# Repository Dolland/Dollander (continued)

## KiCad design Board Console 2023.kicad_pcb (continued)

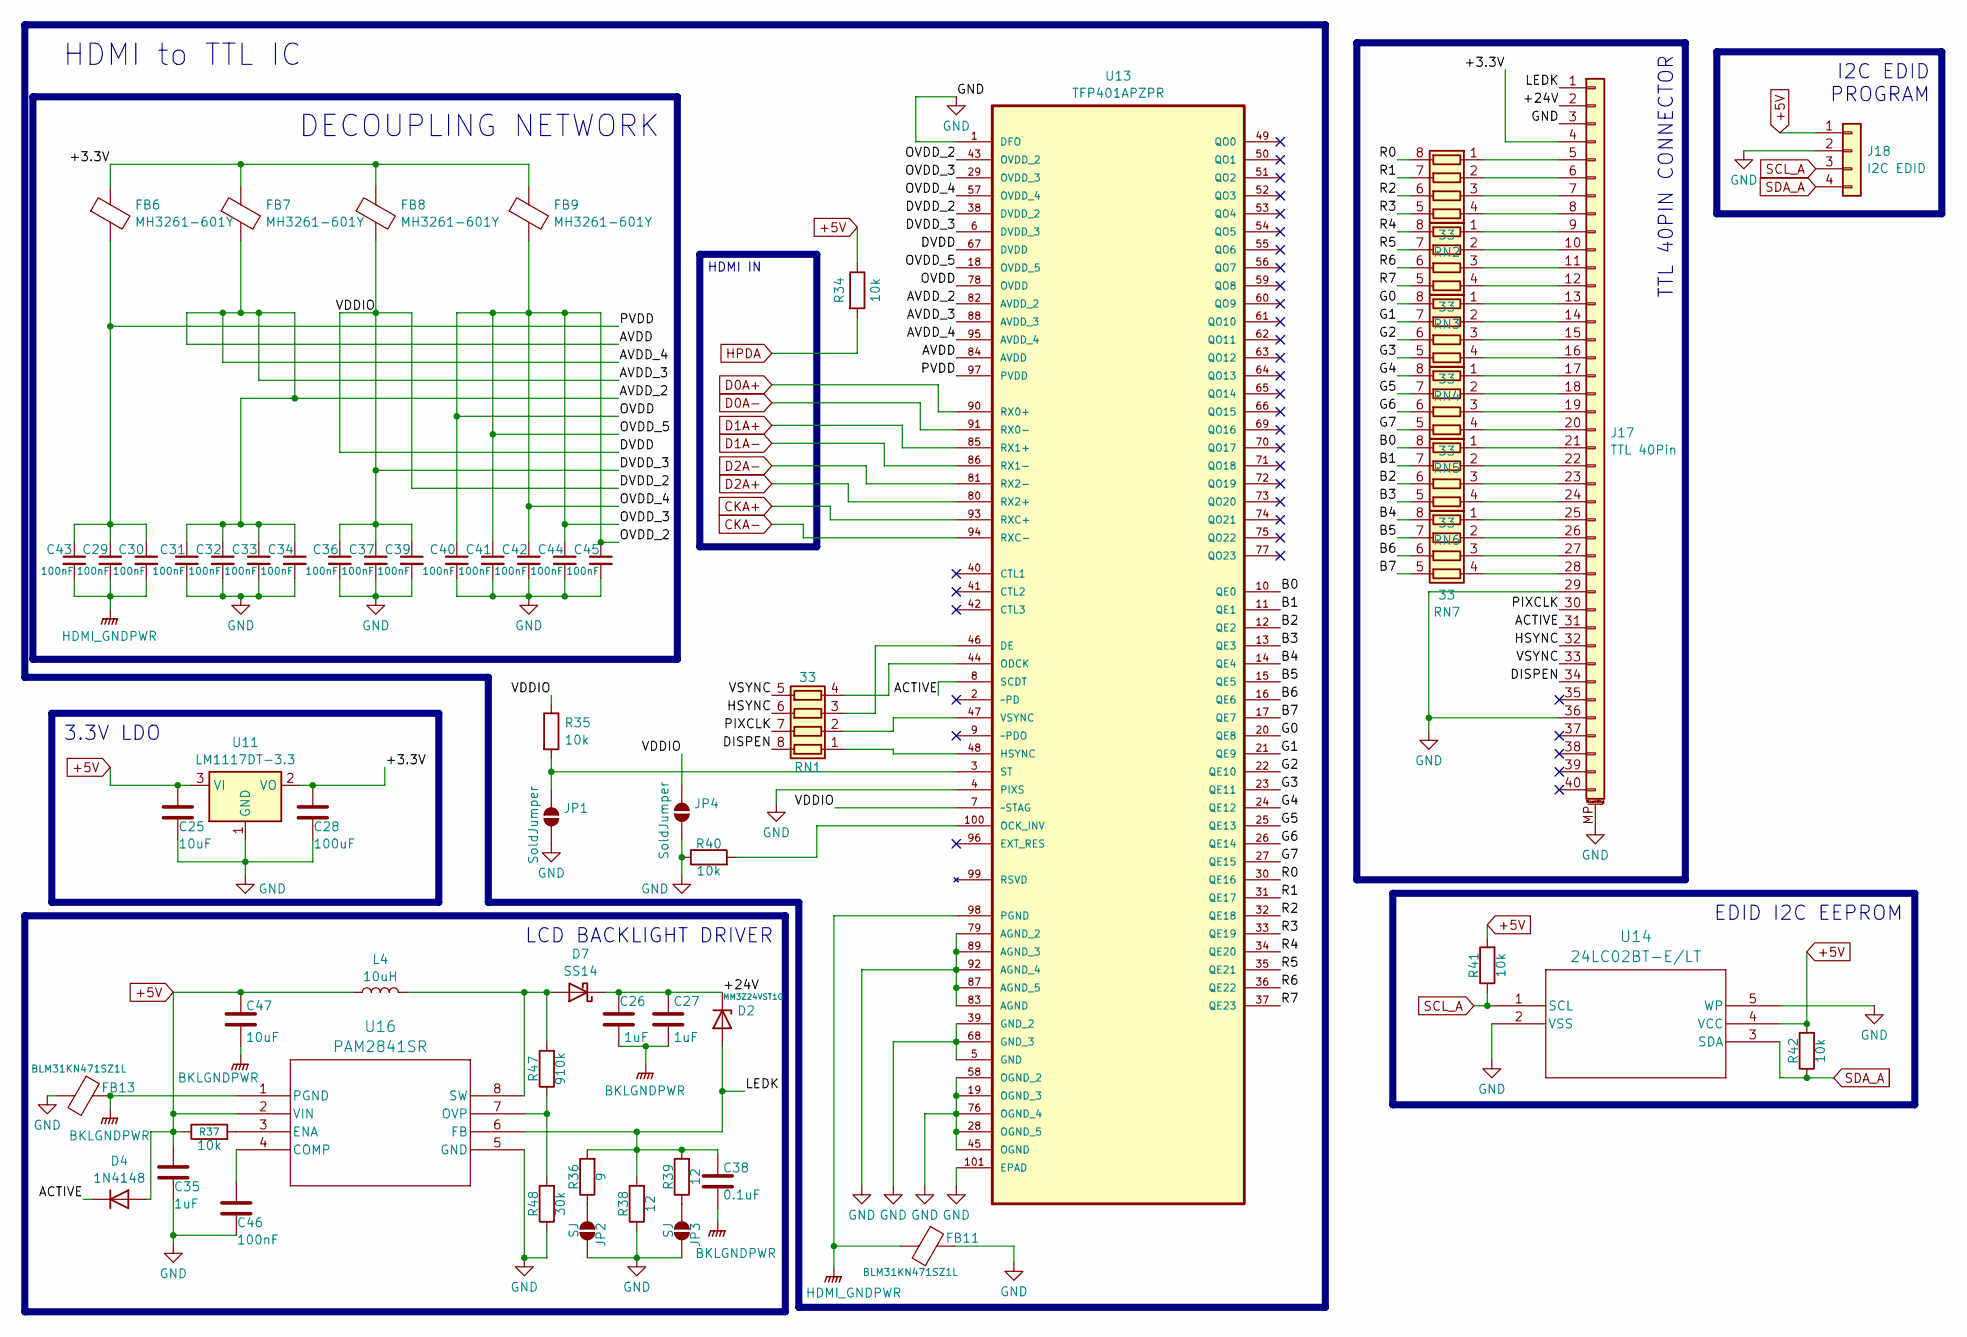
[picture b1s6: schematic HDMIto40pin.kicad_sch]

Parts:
C25, C47: 10uF; C_0603_1608Metric_Pad1.08x0.95mm_HandSolder
C26, C27, C35: 1uF; C_0603_1608Metric_Pad1.08x0.95mm_HandSolder
C28: 100uF; C_1206_3216Metric_Pad1.33x1.80mm_HandSolder
C29, C30, C31, C32, C33, C34, C36, C37, C39, C40, C41, C42, C43, C44, C45, C46: 100nF; C_0603_1608Metric_Pad1.08x0.95mm_HandSolder
C38: 0.1uF; C_0603_1608Metric_Pad1.08x0.95mm_HandSolder
D2: MM3Z24VST1G; D_SOD-123
D4: 1N4148; D_SOD-123
D7: SS14; D_SMA
FB6, FB7, FB8, FB9: MH3261-601Y; L_0805_2012Metric_Pad1.05x1.20mm_HandSolder
FB11, FB13: BLM31KN471SZ1L; L_1206_3216Metric_Pad1.22x1.90mm_HandSolder
J17: TTL 40Pin; Omron_XF2M-4015-1A_1x40-1MP_P0.5mm_Horizontal
J18: I2C EDID; PinHeader_1x04_P2.00mm_Vertical
JP1, JP4: SoldJumper; SolderJumper-2_P1.3mm_Open_Pad1.0x1.5mm
JP2, JP3: SJ; SolderJumper-2_P1.3mm_Open_Pad1.0x1.5mm
L4: 10uH; L_TDK_SLF6025
R34, R35, R37, R40, R41, R42: 10k; R_0603_1608Metric_Pad0.98x0.95mm_HandSolder
R36: 9; R_0603_1608Metric_Pad0.98x0.95mm_HandSolder
R38, R39: 12; R_0603_1608Metric_Pad0.98x0.95mm_HandSolder
R47: 910k; R_0603_1608Metric_Pad0.98x0.95mm_HandSolder
R48: 30k; R_0603_1608Metric_Pad0.98x0.95mm_HandSolder
RN1, RN2, RN3, RN4, RN5, RN6, RN7: 33; EXB28V_PAN
U11: LM1117DT-3.3; SOT-223-3_TabPin2
U13: TFP401APZPR; QFP50P1600X1600X120-101N; MPN TFP401APZPR
U14: 24LC02BT-E/LT; SC70-5_MC_MCH
U16: PAM2841SR; PAM2841

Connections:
+5V: C25.1, C35.1, C47.1, D4.2 (A), J18.1, L4.1, R34.1, R37.1, R41.2, R42.2, U11.3 (VI), U14.4 (VCC), U16.2 (VIN); also elsewhere on the board
/HDMI to Internal Display/+3.3V: C28.1, FB6.1, FB7.1, FB8.1, FB9.1, J17.4, U11.2 (VO)
/HDMI to Internal Display/+24V: C26.1, C27.1, D2.1 (K), D7.1 (K), J17.2
/HDMI to Internal Display/ACTIVE: D4.1 (K), J17.31, U13.8 (SCDT)
/HDMI to Internal Display/AVDD: C31.1, C32.1, C33.1, C34.1, FB7.2, U13.82 (AVDD_2), U13.84 (AVDD), U13.88 (AVDD_3), U13.95 (AVDD_4)
/HDMI to Internal Display/B0: RN6.8 (R1.2), U13.10 (QE0)
/HDMI to Internal Display/B1: RN6.7 (R2.2), U13.11 (QE1)
/HDMI to Internal Display/B2: RN6.6 (R3.2), U13.12 (QE2)
/HDMI to Internal Display/B3: RN6.5 (R4.2), U13.13 (QE3)
/HDMI to Internal Display/B4: RN7.8 (R1.2), U13.14 (QE4)
/HDMI to Internal Display/B5: RN7.7 (R2.2), U13.15 (QE5)
/HDMI to Internal Display/B6: RN7.6 (R3.2), U13.16 (QE6)
/HDMI to Internal Display/B7: RN7.5 (R4.2), U13.17 (QE7)
/HDMI to Internal Display/DISPEN: J17.34, RN1.8 (R1.2)
/HDMI to Internal Display/DVDD: C36.1, C37.1, C39.1, FB8.2, JP4.2 (B), R35.1, U13.6 (DVDD_3), U13.7 (~STAG), U13.38 (DVDD_2), U13.67 (DVDD)
/HDMI to Internal Display/G0: RN4.8 (R1.2), U13.20 (QE8)
/HDMI to Internal Display/G1: RN4.7 (R2.2), U13.21 (QE9)
/HDMI to Internal Display/G2: RN4.6 (R3.2), U13.22 (QE10)
/HDMI to Internal Display/G3: RN4.5 (R4.2), U13.23 (QE11)
/HDMI to Internal Display/G4: RN5.8 (R1.2), U13.24 (QE12)
/HDMI to Internal Display/G5: RN5.7 (R2.2), U13.25 (QE13)
/HDMI to Internal Display/G6: RN5.6 (R3.2), U13.26 (QE14)
/HDMI to Internal Display/G7: RN5.5 (R4.2), U13.27 (QE15)
/HDMI to Internal Display/HSYNC: J17.32, RN1.6 (R3.2)
/HDMI to Internal Display/LEDK: C38.1, D2.2 (A), J17.1, R36.2, R38.2, R39.2, U16.6 (FB)
/HDMI to Internal Display/OVDD: C40.1, C41.1, C42.1, C44.1, C45.1, FB9.2, U13.18 (OVDD_5), U13.29 (OVDD_3), U13.43 (OVDD_2), U13.57 (OVDD_4), U13.78 (OVDD)
/HDMI to Internal Display/PIXCLK: J17.30, RN1.7 (R2.2)
/HDMI to Internal Display/PVDD: C29.1, C30.1, C43.1, FB6.2, U13.97 (PVDD)
/HDMI to Internal Display/R0: RN2.8 (R1.2), U13.30 (QE16)
/HDMI to Internal Display/R1: RN2.7 (R2.2), U13.31 (QE17)
/HDMI to Internal Display/R2: RN2.6 (R3.2), U13.32 (QE18)
/HDMI to Internal Display/R3: RN2.5 (R4.2), U13.33 (QE19)
/HDMI to Internal Display/R4: RN3.8 (R1.2), U13.34 (QE20)
/HDMI to Internal Display/R5: RN3.7 (R2.2), U13.35 (QE21)
/HDMI to Internal Display/R6: RN3.6 (R3.2), U13.36 (QE22)
/HDMI to Internal Display/R7: RN3.5 (R4.2), U13.37 (QE23)
/HDMI to Internal Display/VSYNC: J17.33, RN1.5 (R4.2)
BKLGNDPWR: C26.2, C27.2, C38.2, C47.2, FB13.1, U16.1 (PGND)
CKA+: U13.93 (RXC+); also elsewhere on the board
CKA-: U13.94 (RXC-); also elsewhere on the board
D0A+: U13.90 (RX0+); also elsewhere on the board
D0A-: U13.91 (RX0-); also elsewhere on the board
D1A+: U13.85 (RX1+); also elsewhere on the board
D1A-: U13.86 (RX1-); also elsewhere on the board
D2A+: U13.80 (RX2+); also elsewhere on the board
D2A-: U13.81 (RX2-); also elsewhere on the board
GND: C25.2, C28.2, C31.2, C32.2, C33.2, C34.2, C35.2, C36.2, C37.2, C39.2, C40.2, C41.2, C42.2, C44.2, C45.2, C46.2, FB11.1, FB13.2, J17.3, J17.29, J17.36, J17.MP (MountPin), J18.2, JP1.1 (A), JP2.1 (A), JP3.1 (A), JP4.1 (A), R38.1, R40.1, R48.1, U11.1 (GND), U13.1 (DFO), U13.4 (PIXS), U13.5 (GND), U13.19 (OGND_3), U13.28 (OGND_5), U13.39 (GND_2), U13.45 (OGND), U13.58 (OGND_2), U13.68 (GND_3), U13.76 (OGND_4), U13.79 (AGND_2), U13.83 (AGND), U13.87 (AGND_5), U13.89 (AGND_3), U13.92 (AGND_4), U13.101 (EPAD), U14.2 (VSS), U14.5 (WP), U16.5 (GND); also elsewhere on the board
HDMI_GNDPWR: C29.2, C30.2, C43.2, FB11.2, U13.98 (PGND)
HPDA: R34.2; also elsewhere on the board
unnamed: D7.2 (A), L4.2, R47.2, U16.8 (SW)
unnamed: J17.5, RN2.1 (R1.1)
unnamed: J17.6, RN2.2 (R2.1)
unnamed: J17.7, RN2.3 (R3.1)
unnamed: J17.8, RN2.4 (R4.1)
unnamed: J17.9, RN3.1 (R1.1)
unnamed: J17.10, RN3.2 (R2.1)
unnamed: J17.11, RN3.3 (R3.1)
unnamed: J17.12, RN3.4 (R4.1)
unnamed: J17.13, RN4.1 (R1.1)
unnamed: J17.14, RN4.2 (R2.1)
unnamed: J17.15, RN4.3 (R3.1)
unnamed: J17.16, RN4.4 (R4.1)
unnamed: J17.17, RN5.1 (R1.1)
unnamed: J17.18, RN5.2 (R2.1)
unnamed: J17.19, RN5.3 (R3.1)
unnamed: J17.20, RN5.4 (R4.1)
unnamed: J17.21, RN6.1 (R1.1)
unnamed: J17.22, RN6.2 (R2.1)
unnamed: J17.23, RN6.3 (R3.1)
unnamed: J17.24, RN6.4 (R4.1)
unnamed: J17.25, RN7.1 (R1.1)
unnamed: J17.26, RN7.2 (R2.1)
unnamed: J17.27, RN7.3 (R3.1)
unnamed: J17.28, RN7.4 (R4.1)
unnamed: JP1.2 (B), R35.2, U13.3 (ST)
unnamed: JP2.2 (B), R36.1
unnamed: JP3.2 (B), R39.1
unnamed: RN1.1 (R1.1), U13.48 (HSYNC)
unnamed: RN1.2 (R2.1), U13.47 (VSYNC)
unnamed: RN1.3 (R3.1), U13.46 (DE)
unnamed: RN1.4 (R4.1), U13.44 (ODCK)
unnamed: R40.2, U13.100 (OCK_INV)
unnamed: C46.1, U16.4 (COMP)
unnamed: R37.2, U16.3 (ENA)
unnamed: R47.1, R48.2, U16.7 (OVP)
SCL_A: J18.3, R41.1, U14.1 (SCL); also elsewhere on the board
SDA_A: J18.4, R42.1, U14.3 (SDA); also elsewhere on the board

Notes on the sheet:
LCD BACKLIGHT DRIVER
3.3V LDO
DECOUPLING NETWORK
HDMI IN
EDID I2C EEPROM
I2C EDID PROGRAM
TTL 40PIN CONNECTOR
HDMI to TTL IC

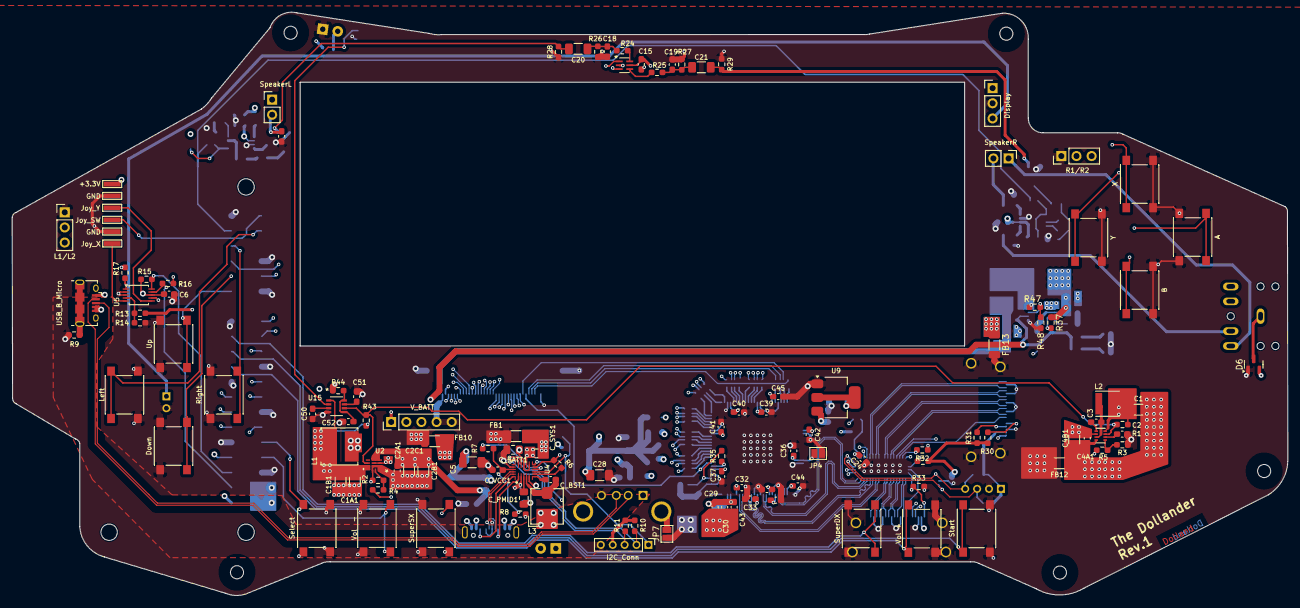
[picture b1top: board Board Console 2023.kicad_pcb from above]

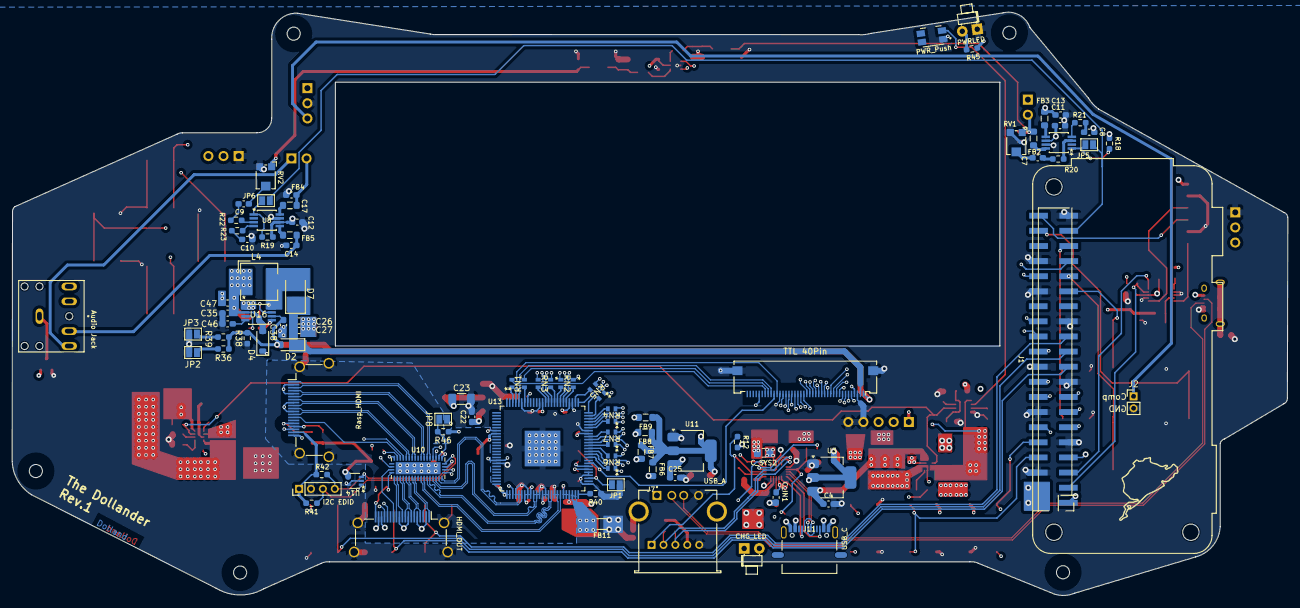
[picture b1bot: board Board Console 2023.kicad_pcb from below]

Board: 6 copper layers, 214.2 x 98.0 mm, 210 parts (84 on the bottom side), 214 nets.

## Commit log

2024-05-19 Added README.md file
2024-05-20 fix joypad area
2024-05-23 fix hdmi traces and push button kill pin supply
2024-05-28 update layout pcb & zip tesi
2024-05-31 edit posizioni porte e di alcune piste
2024-05-31 aggiornato zip tesi
2024-06-01 aggiunto pin enable switch per schermo composito
2024-06-01 update zip tesi
2024-06-01 update impronte
2024-07-20 update zip
